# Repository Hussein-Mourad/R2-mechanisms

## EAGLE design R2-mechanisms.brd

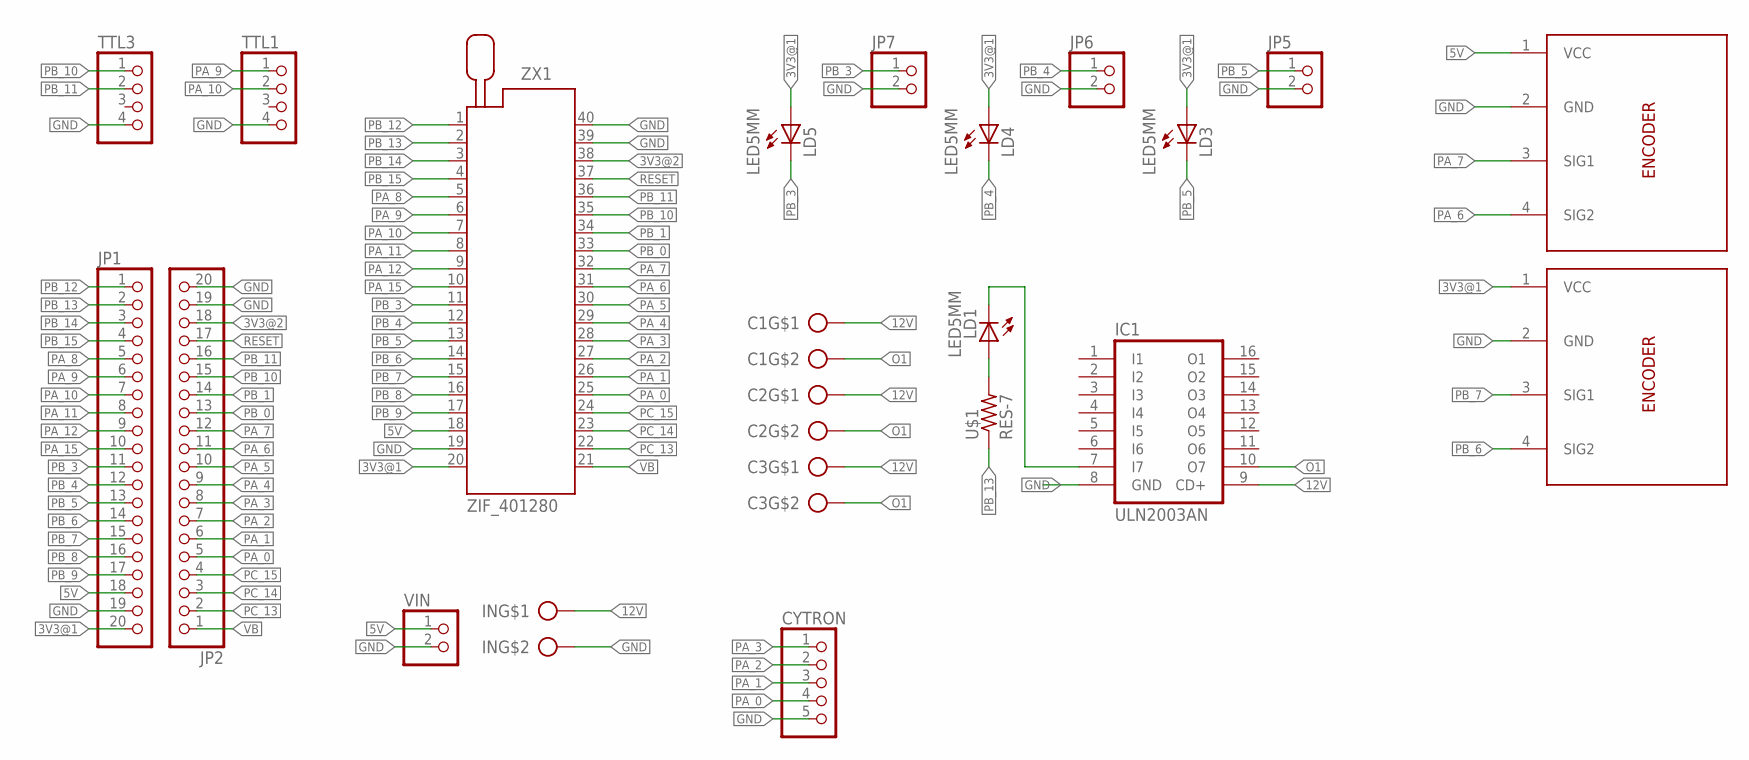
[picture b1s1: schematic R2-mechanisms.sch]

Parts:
C1, C2, C3: CON_PTR_2; AK300/2
CYTRON: PINHD-5_DATA; 1X05_DATA
ENC, ENC1: ENCODER; 1X04_DATA
IC1: ULN2003AN; DIL16
IN: CON_PTR_2; AK300/2
JP1, JP2: PINHD-1X20; 1X20
JP5, JP6, JP7: PINHD-2_DATA; 1X02_DATA
LD1, LD3, LD4, LD5: LED5MM
TTL1, TTL3: PINHD-4_DATA; 1X04_DATA
U$1: RES-7; 0204/7
VIN: PINHD-2_DATA; 1X02_DATA
ZX1: ZIF_401280; 240-1280-00-0602J

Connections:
3V3@1: ENC1.1 (VCC), JP1.20, LD3.A, LD4.A, LD5.A, ZX1.20
3V3@2: JP2.18, ZX1.38
5V: ENC.1 (VCC), JP1.18, VIN.1, ZX1.18
12V: C1.1, C2.1, C3.1, IC1.9 (CD+), IN.1
GND: CYTRON.5, ENC.2 (GND), ENC1.2 (GND), IC1.8 (GND), IN.2, JP1.19, JP2.19, JP2.20, JP5.2, JP6.2, JP7.2, TTL1.4, TTL3.4, VIN.2, ZX1.19, ZX1.39, ZX1.40
unnamed: IC1.7 (I7), LD1.K (C)
unnamed: LD1.A, U$1.2
O1: C1.2, C2.2, C3.2, IC1.10 (O7)
PA_0: CYTRON.4, JP2.5, ZX1.25
PA_1: CYTRON.3, JP2.6, ZX1.26
PA_2: CYTRON.2, JP2.7, ZX1.27
PA_3: CYTRON.1, JP2.8, ZX1.28
PA_4: JP2.9, ZX1.29
PA_5: JP2.10, ZX1.30
PA_6: ENC.4 (SIG2), JP2.11, ZX1.31
PA_7: ENC.3 (SIG1), JP2.12, ZX1.32
PA_8: JP1.5, ZX1.5
PA_9: JP1.6, TTL1.1, ZX1.6
PA_10: JP1.7, TTL1.2, ZX1.7
PA_11: JP1.8, ZX1.8
PA_12: JP1.9, ZX1.9
PA_15: JP1.10, ZX1.10
PB_0: JP2.13, ZX1.33
PB_1: JP2.14, ZX1.34
PB_3: JP1.11, JP7.1, LD5.K (C), ZX1.11
PB_4: JP1.12, JP6.1, LD4.K (C), ZX1.12
PB_5: JP1.13, JP5.1, LD3.K (C), ZX1.13
PB_6: ENC1.4 (SIG2), JP1.14, ZX1.14
PB_7: ENC1.3 (SIG1), JP1.15, ZX1.15
PB_8: JP1.16, ZX1.16
PB_9: JP1.17, ZX1.17
PB_10: JP2.15, TTL3.1, ZX1.35
PB_11: JP2.16, TTL3.2, ZX1.36
PB_12: JP1.1, ZX1.1
PB_13: JP1.2, U$1.1, ZX1.2
PB_14: JP1.3, ZX1.3
PB_15: JP1.4, ZX1.4
PC_13: JP2.2, ZX1.22
PC_14: JP2.3, ZX1.23
PC_15: JP2.4, ZX1.24
RESET: JP2.17, ZX1.37
VB: JP2.1, ZX1.21

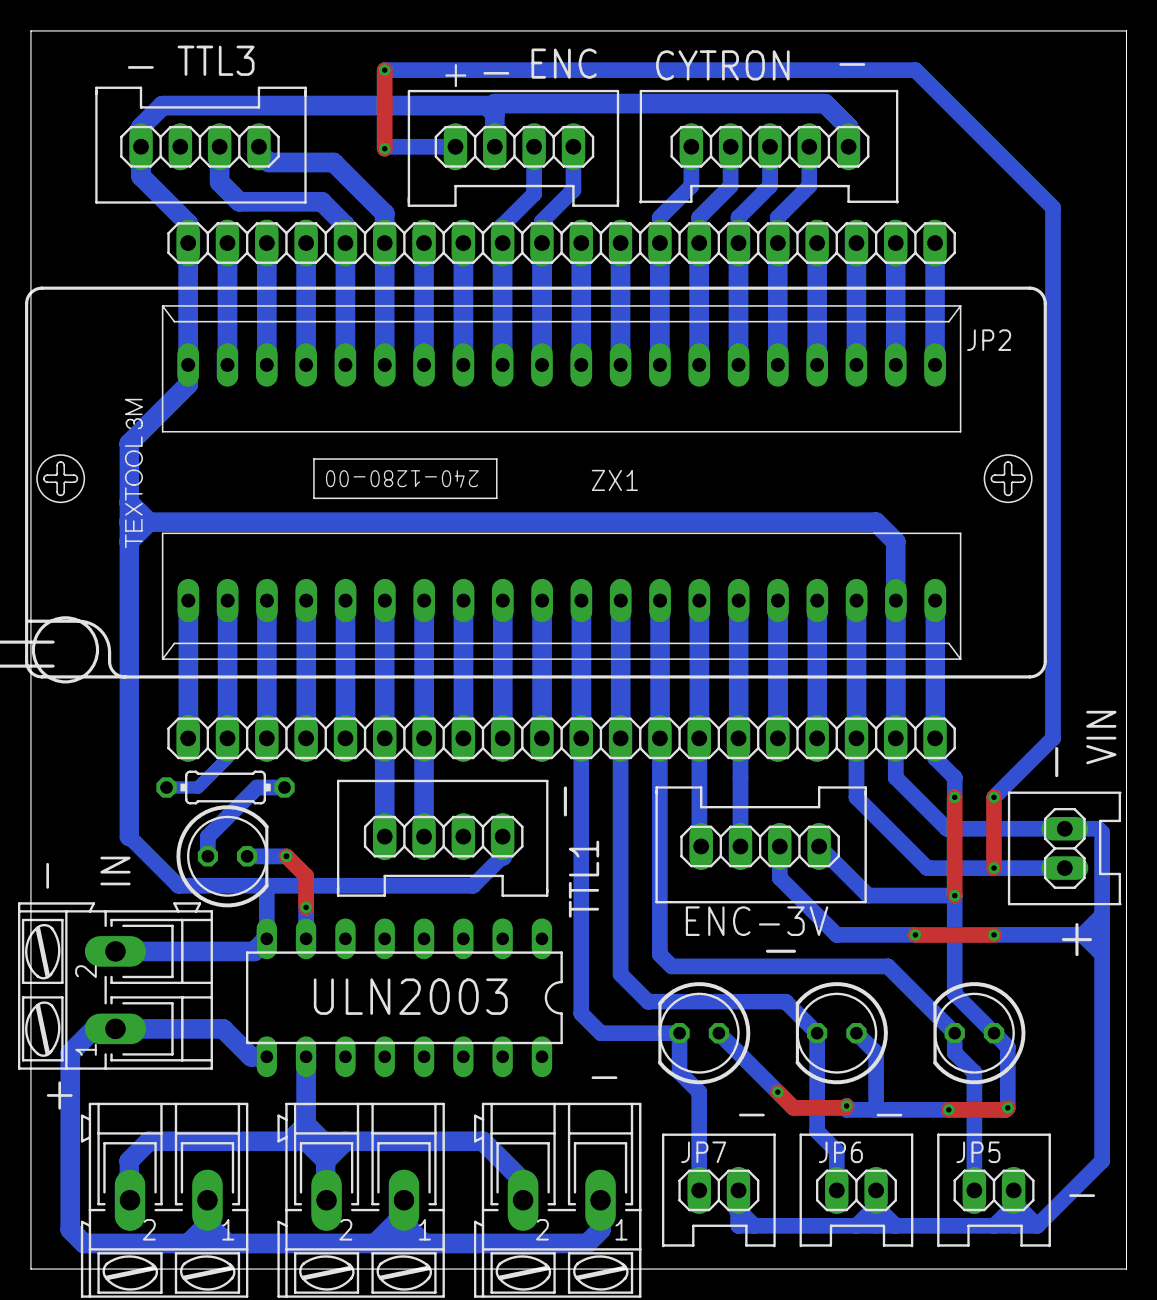
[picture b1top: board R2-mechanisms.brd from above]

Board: 2 copper layers, 70.8 x 80.0 mm, 22 parts (0 on the bottom side), 42 nets.

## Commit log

2022-05-09 Init
